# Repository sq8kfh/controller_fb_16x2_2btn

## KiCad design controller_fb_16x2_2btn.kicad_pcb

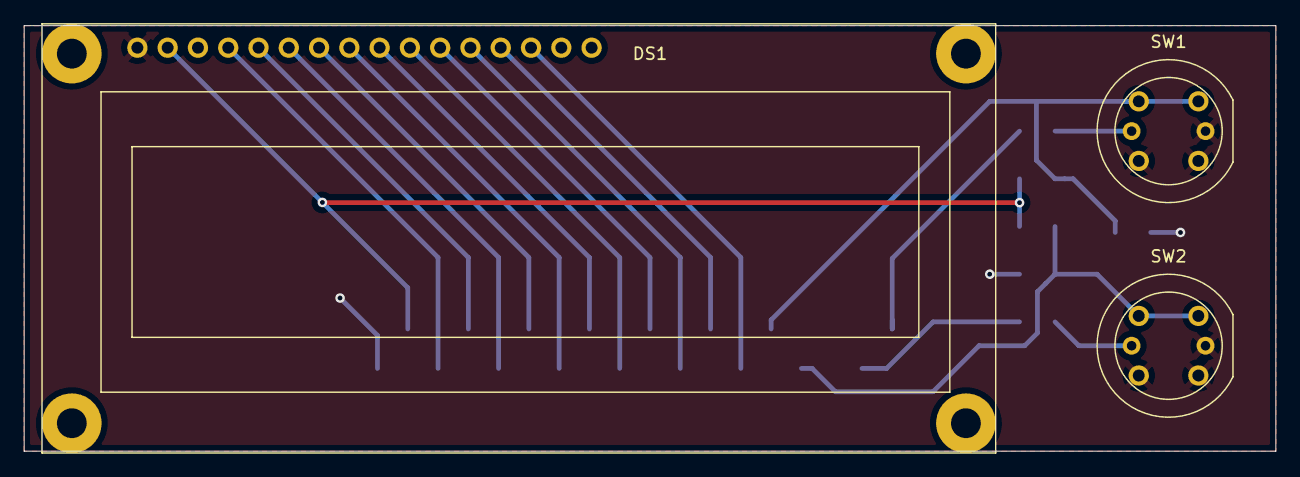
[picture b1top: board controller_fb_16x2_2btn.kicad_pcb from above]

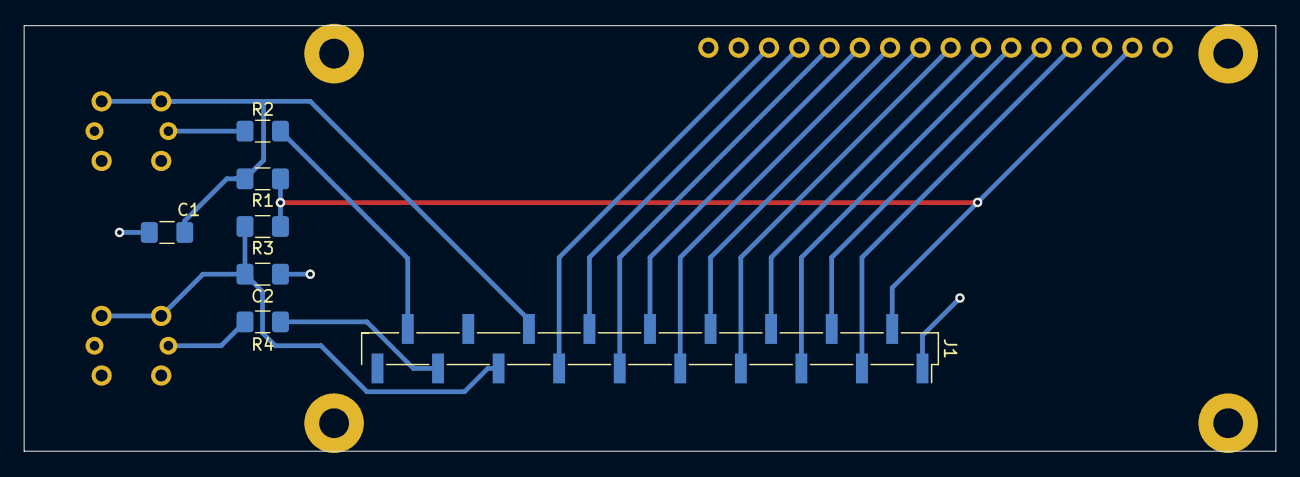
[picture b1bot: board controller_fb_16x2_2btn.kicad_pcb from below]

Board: 2 copper layers, 105.0 x 35.7 mm, 10 parts (7 on the bottom side), 19 nets.

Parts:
C1, C2: 100nF; C_1206_3216Metric_Pad1.42x1.75mm_HandSolder
DS1: RS0010; REC001602A
J1: Conn_01x19; PinHeader_1x19_P2.54mm_Vertical_SMD_Pin1Right
R1, R3: 10k; R_1206_3216Metric_Pad1.42x1.75mm_HandSolder
R2, R4: 470R; R_1206_3216Metric_Pad1.42x1.75mm_HandSolder
SW1, SW2: SW_Push_LED; SW_PUSH_HIGHLY_KS01-BL

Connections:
+5V: DS1.2, J1.2, R1.1, R3.1
/PB0(MISO): DS1.4, J1.3
/PB1(MOSI): DS1.5, J1.4
/PB2(INT1): DS1.10, J1.9
/PB3: C1.2, J1.14, R1.2, SW1.2
/PB4: C2.2, J1.15, R3.2, SW2.2
/PB6: J1.17, R4.2
/PB7(SCK): DS1.6, J1.5
/PC4: DS1.11, J1.10
/PC5: DS1.12, J1.11
/PC6: DS1.13, J1.12
/PC7(D2A): DS1.14, J1.13
/PD0: J1.18, R2.2
/PD5: DS1.7, J1.6
/PD6: DS1.8, J1.7
/PD7: DS1.9, J1.8
GND: C1.1, C2.1, DS1.1, J1.1, SW1.1, SW1.3, SW2.1, SW2.3
unnamed: R2.1, SW1.4
unnamed: R4.1, SW2.4

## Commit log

2020-12-22 init v0.1
2020-12-22 Init v0.2
    - Unifying a button connections
    - Enlarge button holes
    - Decrease PCB high -0.1mm x 2
2022-06-26 Zmiana rozmaru otworów przycisków
2022-06-26 Add production files
